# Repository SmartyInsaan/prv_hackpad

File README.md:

# Prv_HackPad

### Bill of Materials
 - 1x Seeed XIAO RP2040
 - 9x SW_Cherry_MX_1.00u_PCB
 - 9x Blank DSA keycaps
 - Case (from print-legion)
 - 1x Rotary Encoder

### Schematic

---

### PCB 

---

### Case
- Bottom

- Top

## Firmware
For firmware I have used QMK and it was not very easy as we can not write firmware of any hardware unless we have it physically anyways, i'm done with this!

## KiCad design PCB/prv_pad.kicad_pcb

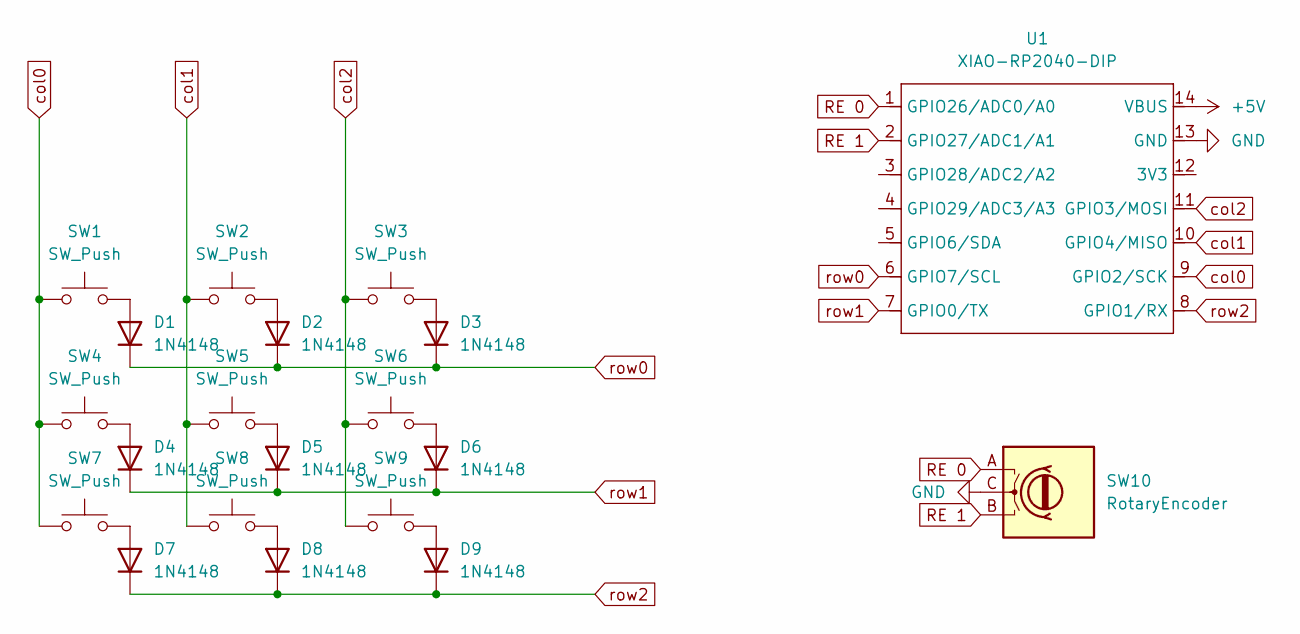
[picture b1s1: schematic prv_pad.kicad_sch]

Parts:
D1, D2, D3, D4, D5, D6, D7, D8, D9: 1N4148; D_DO-35_SOD27_P7.62mm_Horizontal
SW1, SW2, SW3, SW4, SW5, SW6, SW7, SW8, SW9: SW_Push; SW_Cherry_MX_1.00u_PCB
SW10: RotaryEncoder; RotaryEncoder_Alps_EC11E-Switch_Vertical_H20mm
U1: XIAO-RP2040-DIP

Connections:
+5V: U1.14 (VBUS)
GND: SW10.C, U1.13 (GND)
unnamed: D1.2 (A), SW1.2
unnamed: D2.2 (A), SW2.2
unnamed: D3.2 (A), SW3.2
unnamed: D4.2 (A), SW4.2
unnamed: D5.2 (A), SW5.2
unnamed: D6.2 (A), SW6.2
unnamed: D7.2 (A), SW7.2
unnamed: D8.2 (A), SW8.2
unnamed: D9.2 (A), SW9.2
RE 0: SW10.A, U1.1 (GPIO26/ADC0/A0)
RE 1: SW10.B, U1.2 (GPIO27/ADC1/A1)
col0: SW1.1, SW4.1, SW7.1, U1.9 (GPIO2/SCK)
col1: SW2.1, SW5.1, SW8.1, U1.10 (GPIO4/MISO)
col2: SW3.1, SW6.1, SW9.1, U1.11 (GPIO3/MOSI)
row0: D1.1 (K), D2.1 (K), D3.1 (K), U1.6 (GPIO7/SCL)
row1: D4.1 (K), D5.1 (K), D6.1 (K), U1.7 (GPIO0/TX)
row2: D7.1 (K), D8.1 (K), D9.1 (K), U1.8 (GPIO1/RX)

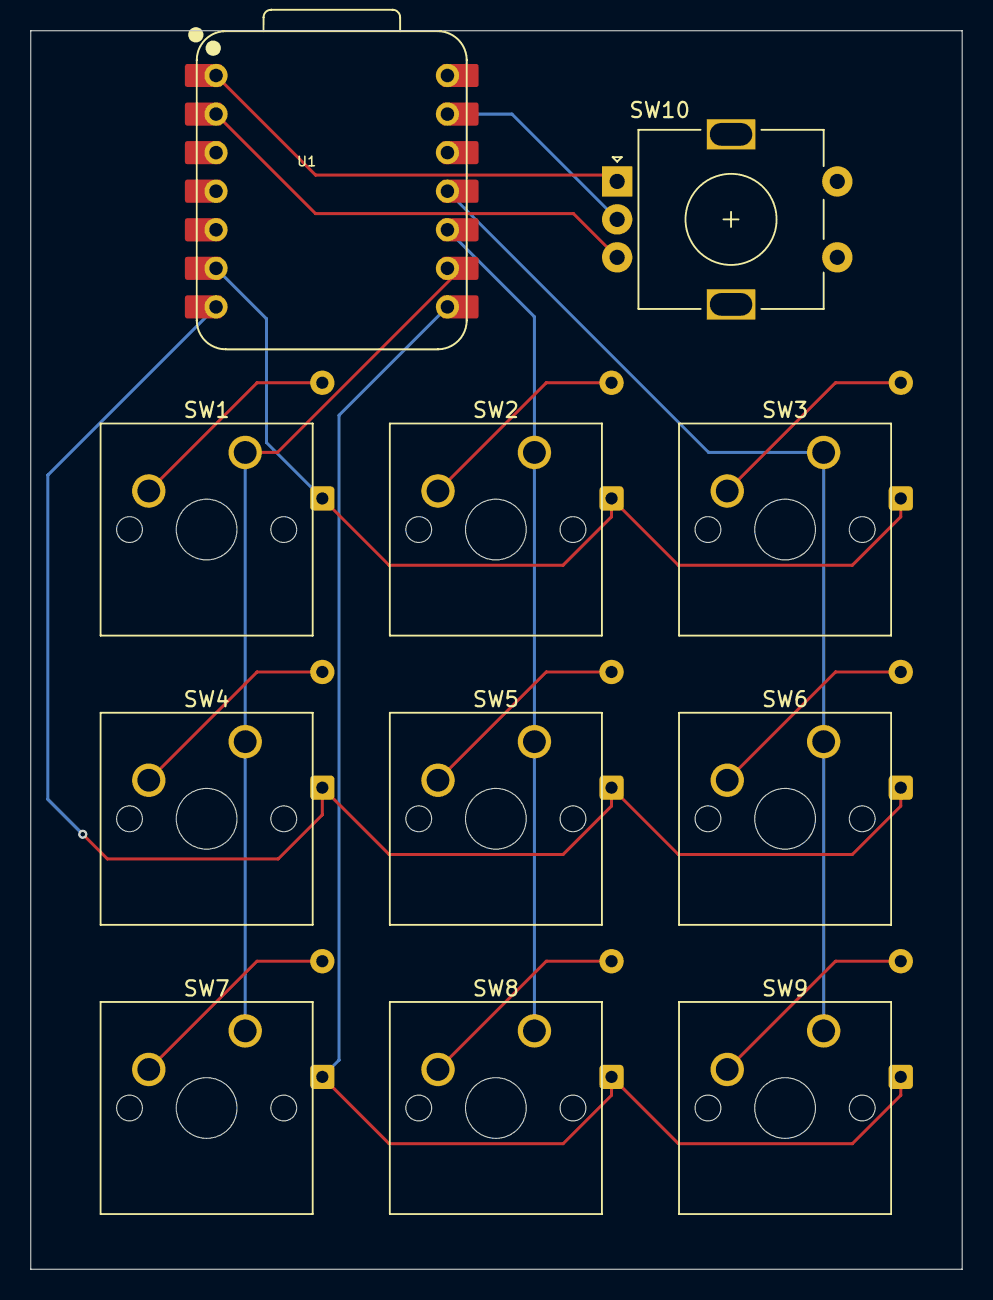
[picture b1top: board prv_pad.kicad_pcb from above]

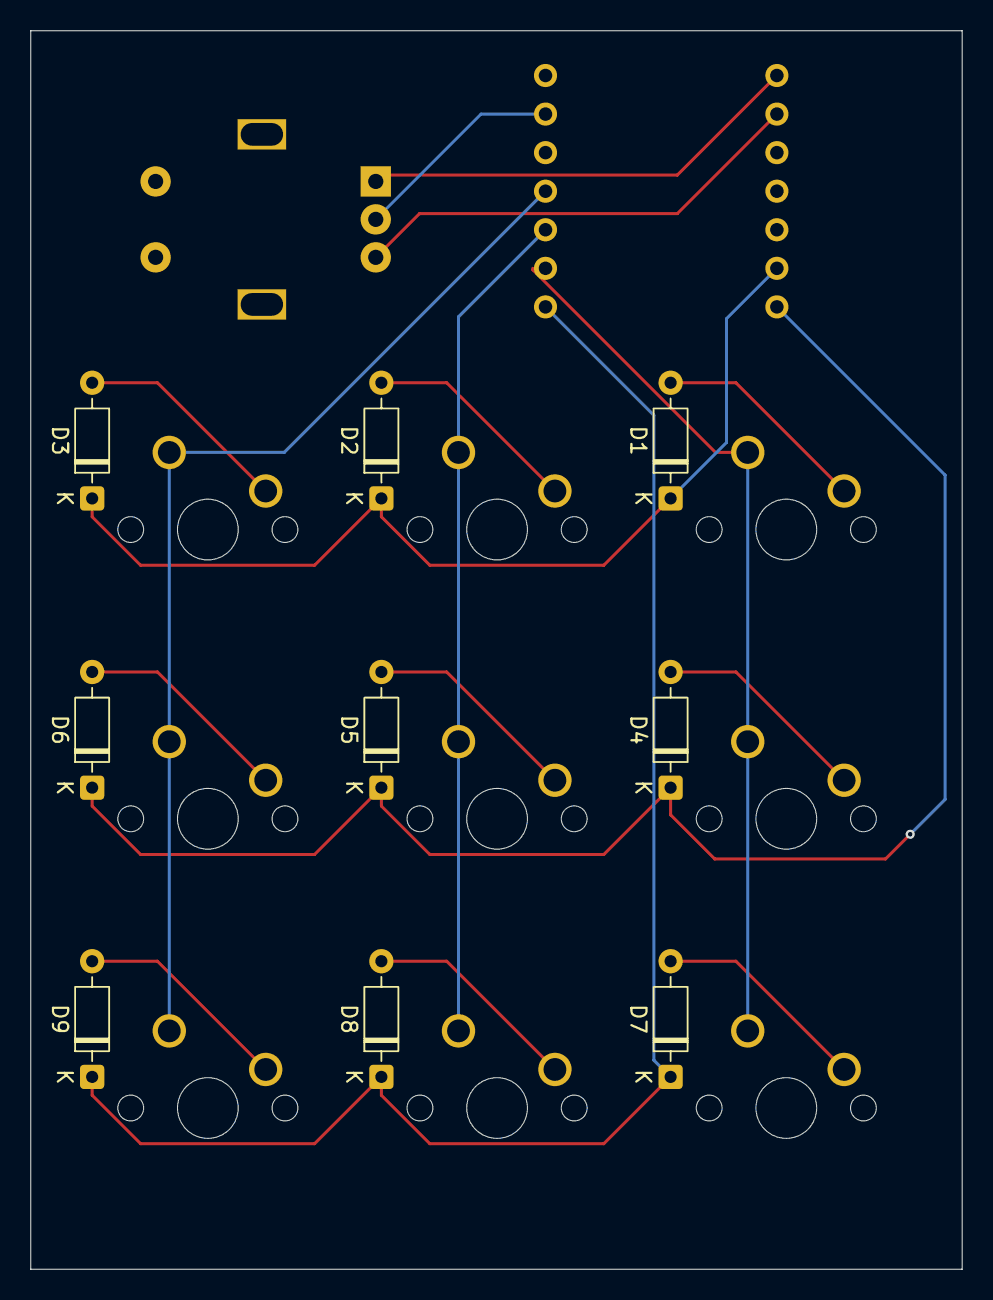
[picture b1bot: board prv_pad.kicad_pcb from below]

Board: 2 copper layers, 61.4 x 81.6 mm, 20 parts (9 on the bottom side), 18 nets.
